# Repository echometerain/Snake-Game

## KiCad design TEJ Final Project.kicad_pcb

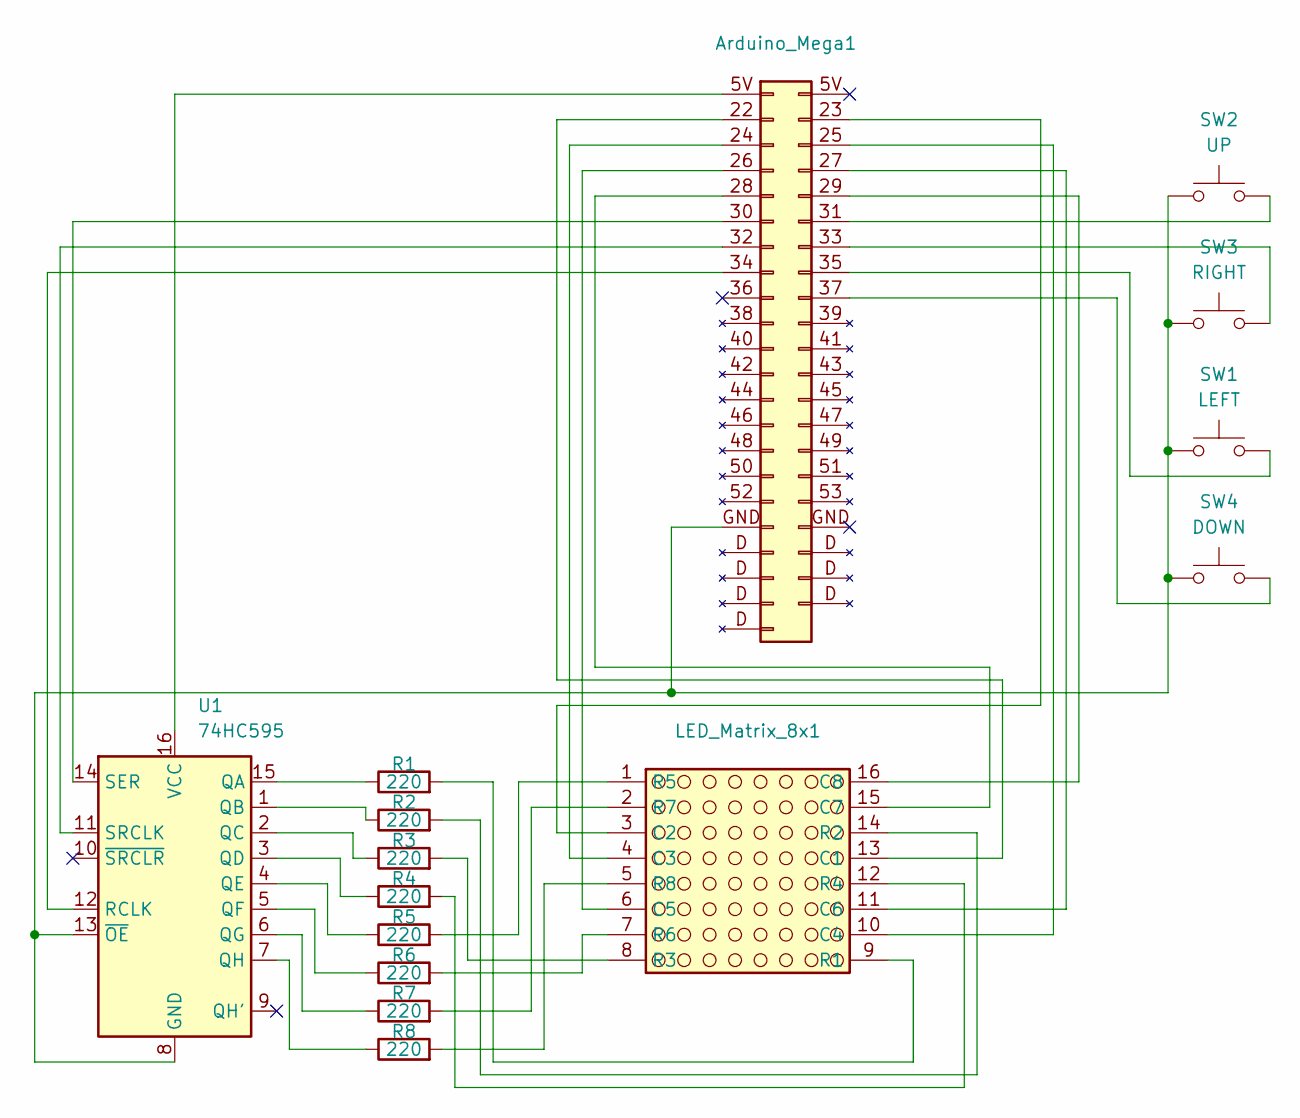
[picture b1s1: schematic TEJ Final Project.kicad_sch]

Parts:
Arduino_Mega1: Arduino Mega
LED_Matrix_8x1: LED Matrix
R1, R2, R3, R4, R5, R6, R7, R8: 220; R_Axial_DIN0207_L6.3mm_D2.5mm_P10.16mm_Horizontal
SW1: LEFT; SW_PUSH_6mm
SW2: UP; SW_PUSH_6mm
SW3: RIGHT; SW_PUSH_6mm
SW4: DOWN; SW_PUSH_6mm
U1: 74HC595; CERDIP-16_W7.62mm_SideBrazed_LongPads

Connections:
unnamed: Arduino_Mega1.31, SW2.2
unnamed: Arduino_Mega1.33, SW3.2
unnamed: Arduino_Mega1.35, SW1.2
unnamed: Arduino_Mega1.37, SW4.2
unnamed: Arduino_Mega1.22, LED_Matrix_8x1.13 (C1)
unnamed: Arduino_Mega1.23, LED_Matrix_8x1.3 (C2)
unnamed: Arduino_Mega1.24, LED_Matrix_8x1.4 (C3)
unnamed: Arduino_Mega1.25, LED_Matrix_8x1.10 (C4)
unnamed: Arduino_Mega1.26, LED_Matrix_8x1.6 (C5)
unnamed: Arduino_Mega1.27, LED_Matrix_8x1.11 (C6)
unnamed: Arduino_Mega1.28, LED_Matrix_8x1.15 (C7)
unnamed: Arduino_Mega1.29, LED_Matrix_8x1.16 (C8)
unnamed: LED_Matrix_8x1.9 (R1), R1.2
unnamed: LED_Matrix_8x1.14 (R2), R2.2
unnamed: LED_Matrix_8x1.8 (R3), R3.2
unnamed: LED_Matrix_8x1.12 (R4), R4.2
unnamed: LED_Matrix_8x1.1 (R5), R5.2
unnamed: LED_Matrix_8x1.7 (R6), R6.2
unnamed: LED_Matrix_8x1.2 (R7), R7.2
unnamed: LED_Matrix_8x1.5 (R8), R8.2
unnamed: Arduino_Mega1.GND, SW1.1, SW2.1, SW3.1, SW4.1, U1.8 (GND), U1.13 (~OE)
unnamed: R1.1, U1.15 (QA)
unnamed: R2.1, U1.1 (QB)
unnamed: R3.1, U1.2 (QC)
unnamed: R4.1, U1.3 (QD)
unnamed: R5.1, U1.4 (QE)
unnamed: R6.1, U1.5 (QF)
unnamed: R7.1, U1.6 (QG)
unnamed: R8.1, U1.7 (QH)
unnamed: Arduino_Mega1.34, U1.12 (RCLK)
unnamed: Arduino_Mega1.30, U1.14 (SER)
unnamed: Arduino_Mega1.32, U1.11 (SRCLK)
unnamed: Arduino_Mega1.5V, U1.16 (VCC)

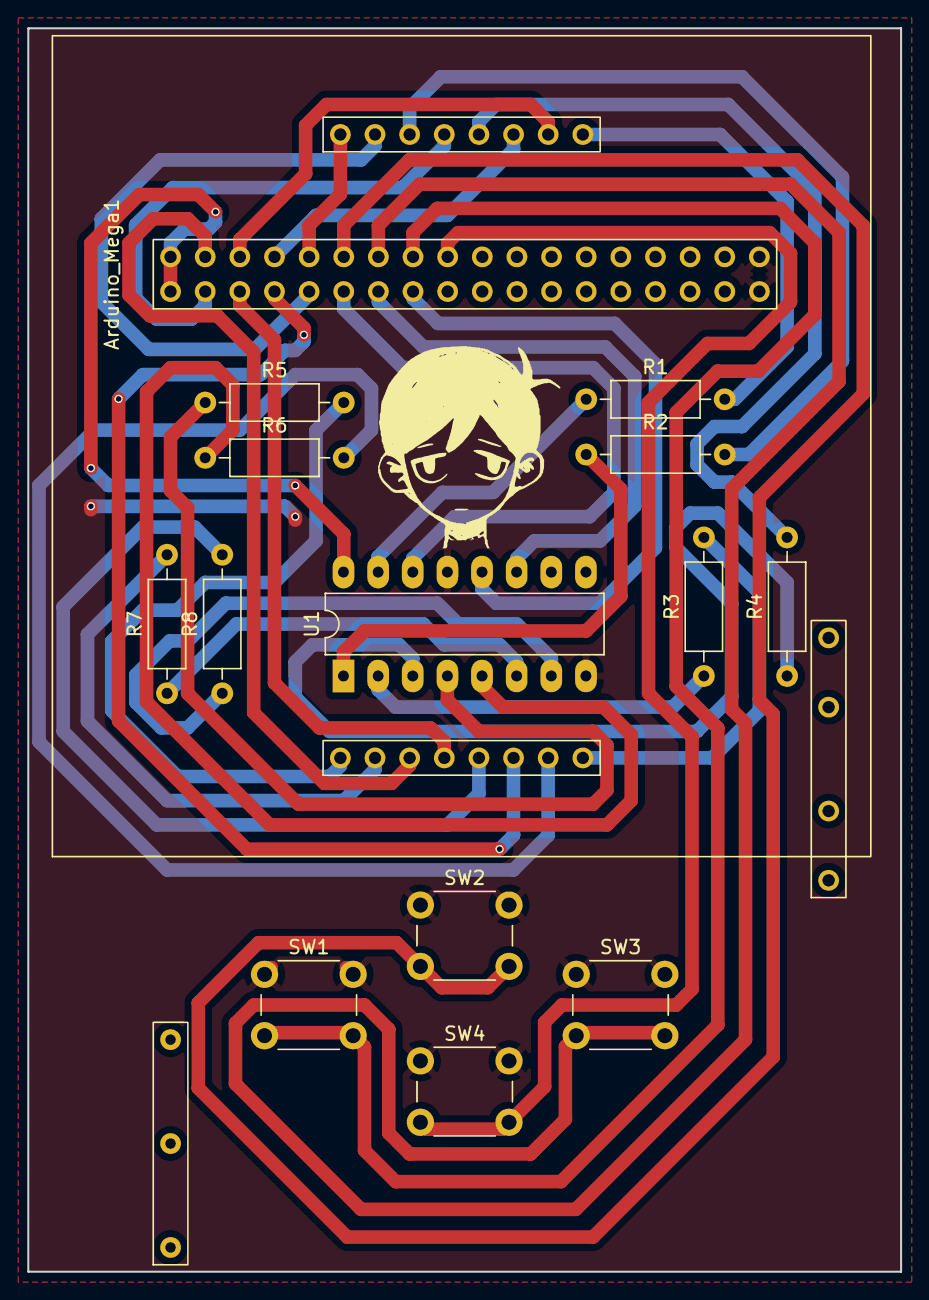
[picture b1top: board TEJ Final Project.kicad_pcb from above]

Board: 2 copper layers, 64.0 x 91.2 mm, 15 parts (0 on the bottom side), 33 nets.

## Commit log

2024-09-18 Add screenshots
